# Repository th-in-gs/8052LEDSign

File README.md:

# MSM83C154 ROM Dump

A dump and analysis of the 16 KB internal mask ROM of an OKI MSM83C154
(8051-family) microcontroller, found among the pile of MCS-51 parts in my
[makerspace](https://ashevillemakers.org/)'s electronics supply drawers.

The chips turned out to be preprogrammed. This repository contains the tooling
used to read the ROM out, the dump itself, and an analysis of what the program
does.

A second set of chips from the same drawer, Signetics SCN8031Hs, is covered
in `scn8031/`. They are marked as the ROMless 8031, but their 4 KB internal
ROM holds a stepper motor controller program.

It is a branch of my 8052 LED sign project, which provided the hardware: an
8052 running from SRAM that an ATmega328 loads on its behalf. I'm documenting
that project on my blog,
https://www.blog.montgomerie.net/tags/makerspace-mcu-series/.

## Contents

| Path | What |
|---|---|
| `romdump.bin` | The 16,384-byte ROM dump. Its internal checksum verifies. |
| `ROM_ANALYSIS.md` | What the program does. |
| `romdump_annotated.lst` | Annotated disassembly. |
| `tools/dis51.py` | Minimal recursive-descent 8051 disassembler used for the analysis. |
| `tools/annotate.py` | Generator for the annotated disassemblies. `--annotations MODULE` picks the annotation data. |
| `tools/romdump_annotations.py` | Annotation data for the OKI dump (the default). |
| `scn8031/` | The SCN8031H dump, its analysis and annotated disassembly. |
| `tools/scn8031_annotations.py` | Annotation data for the SCN8031H dump. |
| `mcs51/src/romdump.c` | Dumper, run by the 8052. |
| `avr_host/src/` | AVR host: loads the dumper, runs it, prints the dump over serial. |
| `scripts/capture_romdump.py` | Captures the serial output into a `.bin` file (default `romdump.bin`). |
| `hardware/` | KiCad schematic and PCB of the circuit. |
| `docs/RAM:ROM Shadowing.txt` | Notes on the SRAM address decode the dumper relies on. |

## How the dump works

The MSM83C154 does not latch its EA (External Access) pin at reset, so the
internal ROM can be switched on after the chip has started running external
code:

1. The AVR writes the dumper to SRAM at code address 0x4000, and a stub
   `LJMP 0x4000` at 0x0000.
2. With EA held low, the AVR releases the 8052's reset. The 8052 runs the stub
   from external memory and jumps to the dumper.
3. The AVR raises EA. Code addresses 0x0000–0x3FFF now read the internal ROM.
   Code at 0x4000 and above is still fetched externally.
4. The dumper copies code 0x0000–0x3FFF (MOVC) to data 0x0000–0x3FFF (MOVX).
5. The AVR puts the 8052 back into reset, reads the SRAM, and prints it.

The 8052's EA pin must be wired to AVR pin PD2.

## Running it

This is built with [PlatformIO](https://platformio.org). On Apple Silicon Macs,
PlatformIO's MCS-51 and AVR toolchains need Rosetta.

```
pio run -e mcs51 -t upload
~/.platformio/penv/bin/python scripts/capture_romdump.py [port] [output.bin]
```

Uploading the `mcs51` environment builds the dumper, then builds and uploads
the AVR host with the dumper compiled into it. The capture script resets the
AVR, so the whole sequence (RAM test, load, dump) runs again while it listens.
The serial monitor runs at 38400 baud.

# Copyright

Copyright 2026 James Montgomerie.

See `LICENSE.txt` for license terms.

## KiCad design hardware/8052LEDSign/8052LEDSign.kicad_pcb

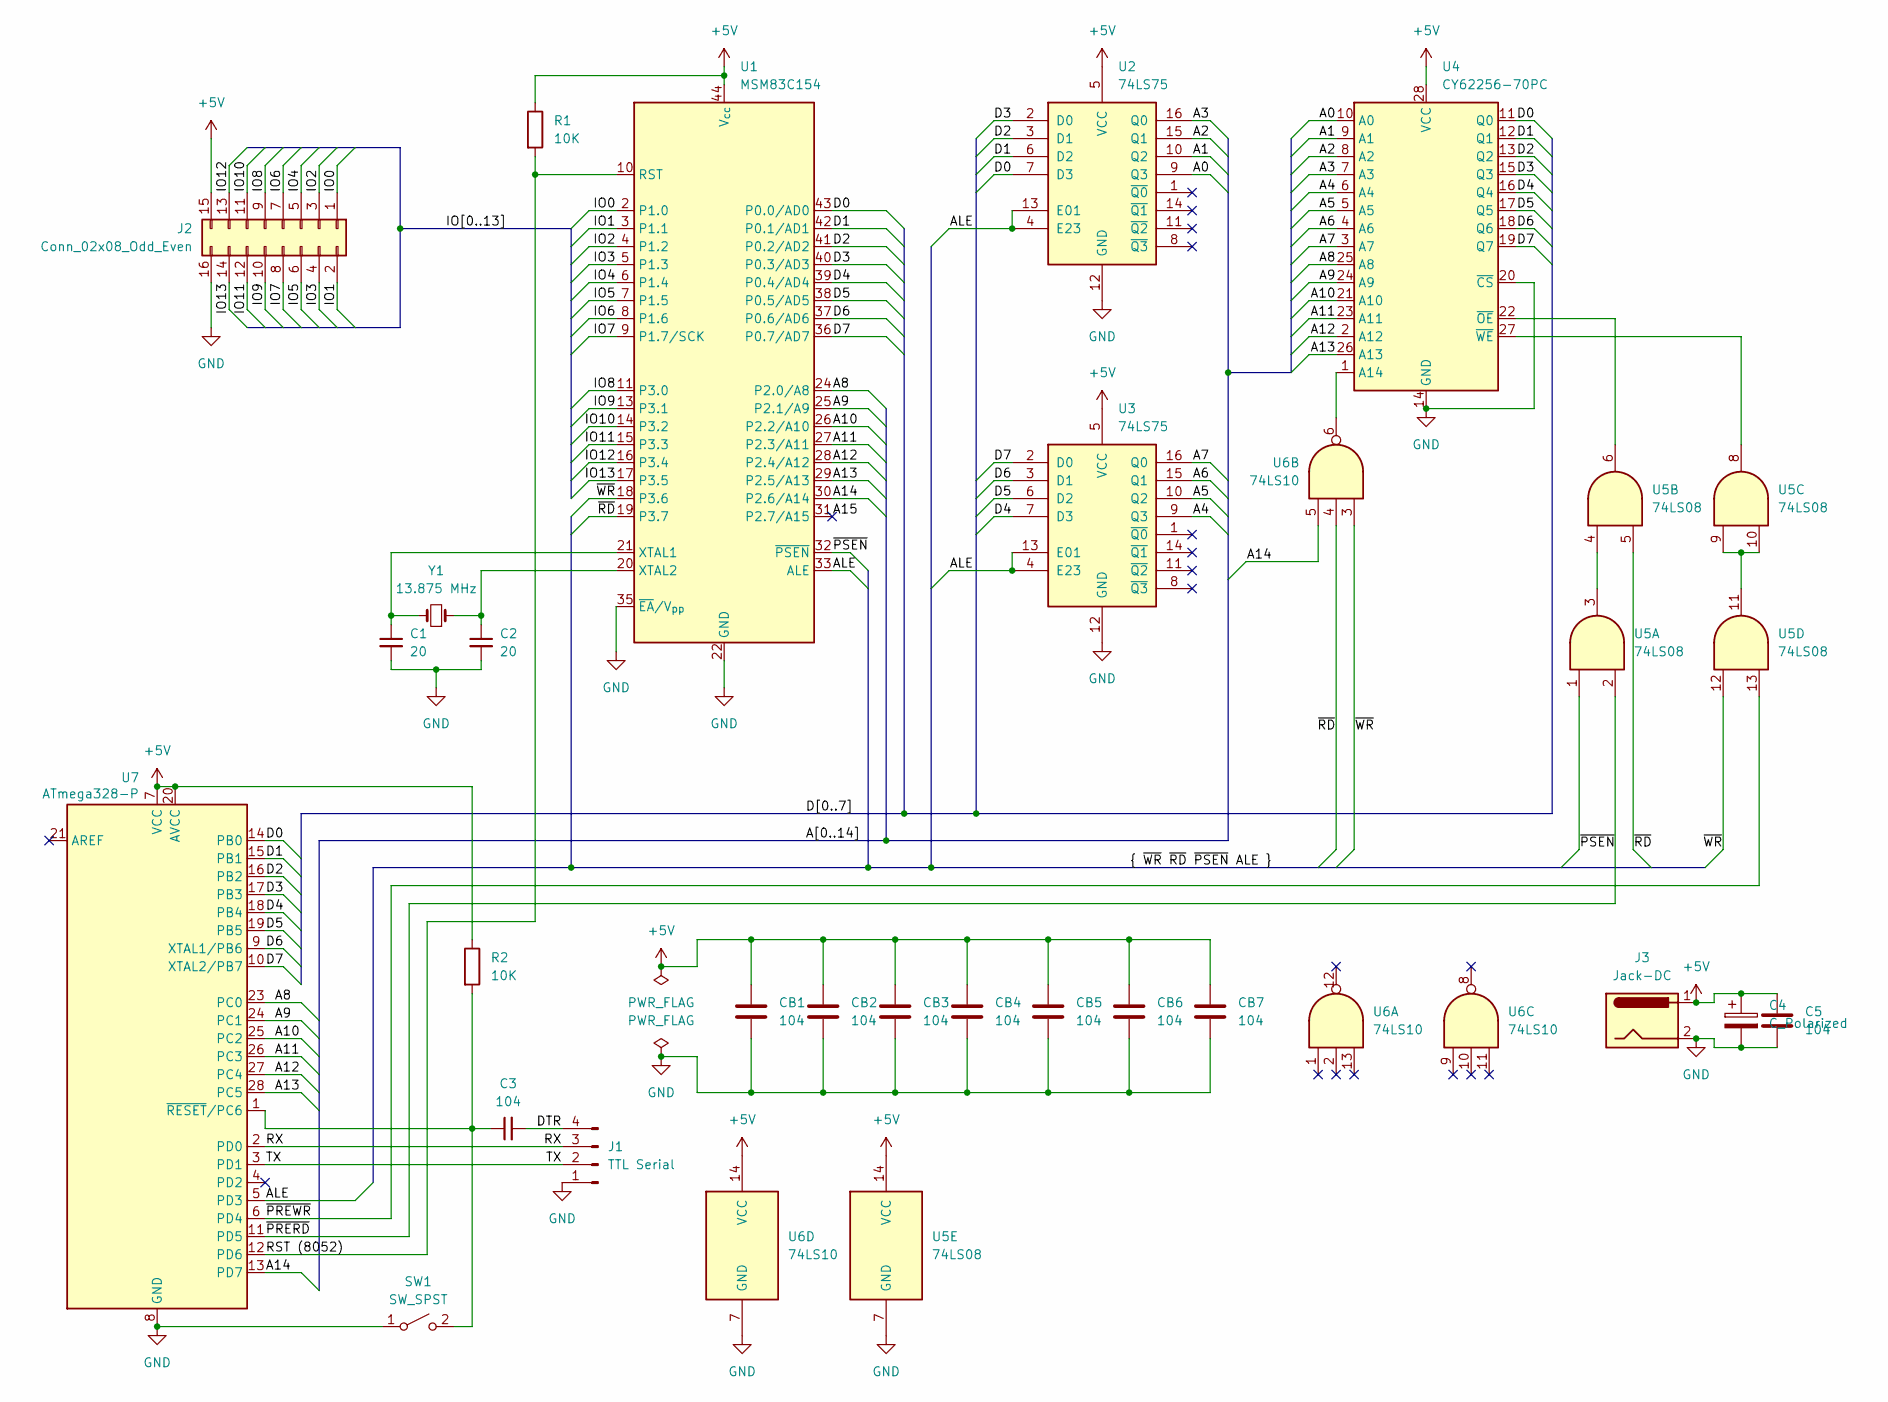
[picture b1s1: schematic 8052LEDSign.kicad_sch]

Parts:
C1, C2: 20; C_Disc_D3.0mm_W1.6mm_P2.50mm
C3, C5: 104; C_Disc_D3.0mm_W1.6mm_P2.50mm
C4: C_Polarized; CP_Radial_D6.3mm_P2.50mm
CB1, CB2, CB3, CB4, CB5, CB6, CB7: 104; C_Disc_D3.0mm_W1.6mm_P2.50mm
J1: TTL Serial; PinSocket_1x04_P2.54mm_Vertical
J2: Conn_02x08_Odd_Even; PinSocket_2x08_P2.54mm_Vertical
J3: Jack-DC; BarrelJack_Horizontal
R1, R2: 10K; R_Axial_DIN0207_L6.3mm_D2.5mm_P10.16mm_Horizontal
SW1: SW_SPST; SW_PUSH_6mm
U1: MSM83C154; PLCC-44_THT-Socket
U2, U3: 74LS75; DIP-16_W7.62mm_Socket
U4: CY62256-70PC; DIP-28_W15.24mm
U5: 74LS08; DIP-14_W7.62mm_Socket
U6: 74LS10; DIP-14_W7.62mm_Socket
U7: ATmega328-P; DIP-28_W7.62mm
Y1: 13.875 MHz; Crystal_HC50_Horizontal

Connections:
+5V: C4.1, C5.1, CB1.1, CB2.1, CB3.1, CB4.1, CB5.1, CB6.1, CB7.1, J2.15, J3.1, R1.1, R2.1, U1.44 (V_{cc}), U2.5 (VCC), U3.5 (VCC), U4.28 (VCC), U5.14 (VCC), U6.14 (VCC), U7.7 (VCC), U7.20 (AVCC)
/A0: U2.9 (Q3), U4.10 (A0)
/A1: U2.10 (Q2), U4.9 (A1)
/A2: U2.15 (Q1), U4.8 (A2)
/A3: U2.16 (Q0), U4.7 (A3)
/A4: U3.9 (Q3), U4.6 (A4)
/A5: U3.10 (Q2), U4.5 (A5)
/A6: U3.15 (Q1), U4.4 (A6)
/A7: U3.16 (Q0), U4.3 (A7)
/A8: U1.24 (P2.0/A8), U4.25 (A8), U7.23 (PC0)
/A9: U1.25 (P2.1/A9), U4.24 (A9), U7.24 (PC1)
/A10: U1.26 (P2.2/A10), U4.21 (A10), U7.25 (PC2)
/A11: U1.27 (P2.3/A11), U4.23 (A11), U7.26 (PC3)
/A12: U1.28 (P2.4/A12), U4.2 (A12), U7.27 (PC4)
/A13: U1.29 (P2.5/A13), U4.26 (A13), U7.28 (PC5)
/A14: U1.30 (P2.6/A14), U6.5, U7.13 (PD7)
/A15: U1.31 (P2.7/A15)
/ALE: U1.33 (ALE), U2.4 (E23), U2.13 (E01), U3.4 (E23), U3.13 (E01), U7.5 (PD3)
/D0: U1.43 (P0.0/AD0), U2.7 (D3), U4.11 (Q0), U7.14 (PB0)
/D1: U1.42 (P0.1/AD1), U2.6 (D2), U4.12 (Q1), U7.15 (PB1)
/D2: U1.41 (P0.2/AD2), U2.3 (D1), U4.13 (Q2), U7.16 (PB2)
/D3: U1.40 (P0.3/AD3), U2.2 (D0), U4.15 (Q3), U7.17 (PB3)
/D4: U1.39 (P0.4/AD4), U3.7 (D3), U4.16 (Q4), U7.18 (PB4)
/D5: U1.38 (P0.5/AD5), U3.6 (D2), U4.17 (Q5), U7.19 (PB5)
/D6: U1.37 (P0.6/AD6), U3.3 (D1), U4.18 (Q6), U7.9 (XTAL1/PB6)
/D7: U1.36 (P0.7/AD7), U3.2 (D0), U4.19 (Q7), U7.10 (XTAL2/PB7)
/DTR: C3.2, J1.4
/IO0: J2.1, U1.2 (P1.0)
/IO1: J2.2, U1.3 (P1.1)
/IO2: J2.3, U1.4 (P1.2)
/IO3: J2.4, U1.5 (P1.3)
/IO4: J2.5, U1.6 (P1.4)
/IO5: J2.6, U1.7 (P1.5)
/IO6: J2.7, U1.8 (P1.6)
/IO7: J2.8, U1.9 (P1.7/SCK)
/IO8: J2.9, U1.11 (P3.0)
/IO9: J2.10, U1.13 (P3.1)
/IO10: J2.11, U1.14 (P3.2)
/IO11: J2.12, U1.15 (P3.3)
/IO12: J2.13, U1.16 (P3.4)
/IO13: J2.14, U1.17 (P3.5)
/RST (8052): R1.2, U1.10 (RST), U7.12 (PD6)
/RX: J1.3, U7.2 (PD0)
/TX: J1.2, U7.3 (PD1)
/~PRERD: U5.2, U7.11 (PD5)
/~PREWR: U5.13, U7.6 (PD4)
/~PSEN: U1.32 (~PSEN), U5.1
/~RD: U1.19 (P3.7), U5.5, U6.4
/~WR: U1.18 (P3.6), U5.12, U6.3
GND: C1.2, C2.2, C4.2, C5.2, CB1.2, CB2.2, CB3.2, CB4.2, CB5.2, CB6.2, CB7.2, J1.1, J2.16, J3.2, SW1.1 (A), U1.22 (GND), U1.35 (~EA/V_{pp}), U2.12 (GND), U3.12 (GND), U4.14 (GND), U4.20 (~CS), U5.7 (GND), U6.7 (GND), U7.8 (GND), U7.22 (GND)
unnamed: C3.1, R2.2, SW1.2 (B), U7.1 (~RESET/PC6)
unnamed: C1.1, U1.21 (XTAL1), Y1.2
unnamed: C2.1, U1.20 (XTAL2), Y1.1
unnamed: U4.1 (A14), U6.6
unnamed: U4.22 (~OE), U5.6
unnamed: U4.27 (~WE), U5.8
unnamed: U5.3, U5.4
unnamed: U5.9, U5.10, U5.11

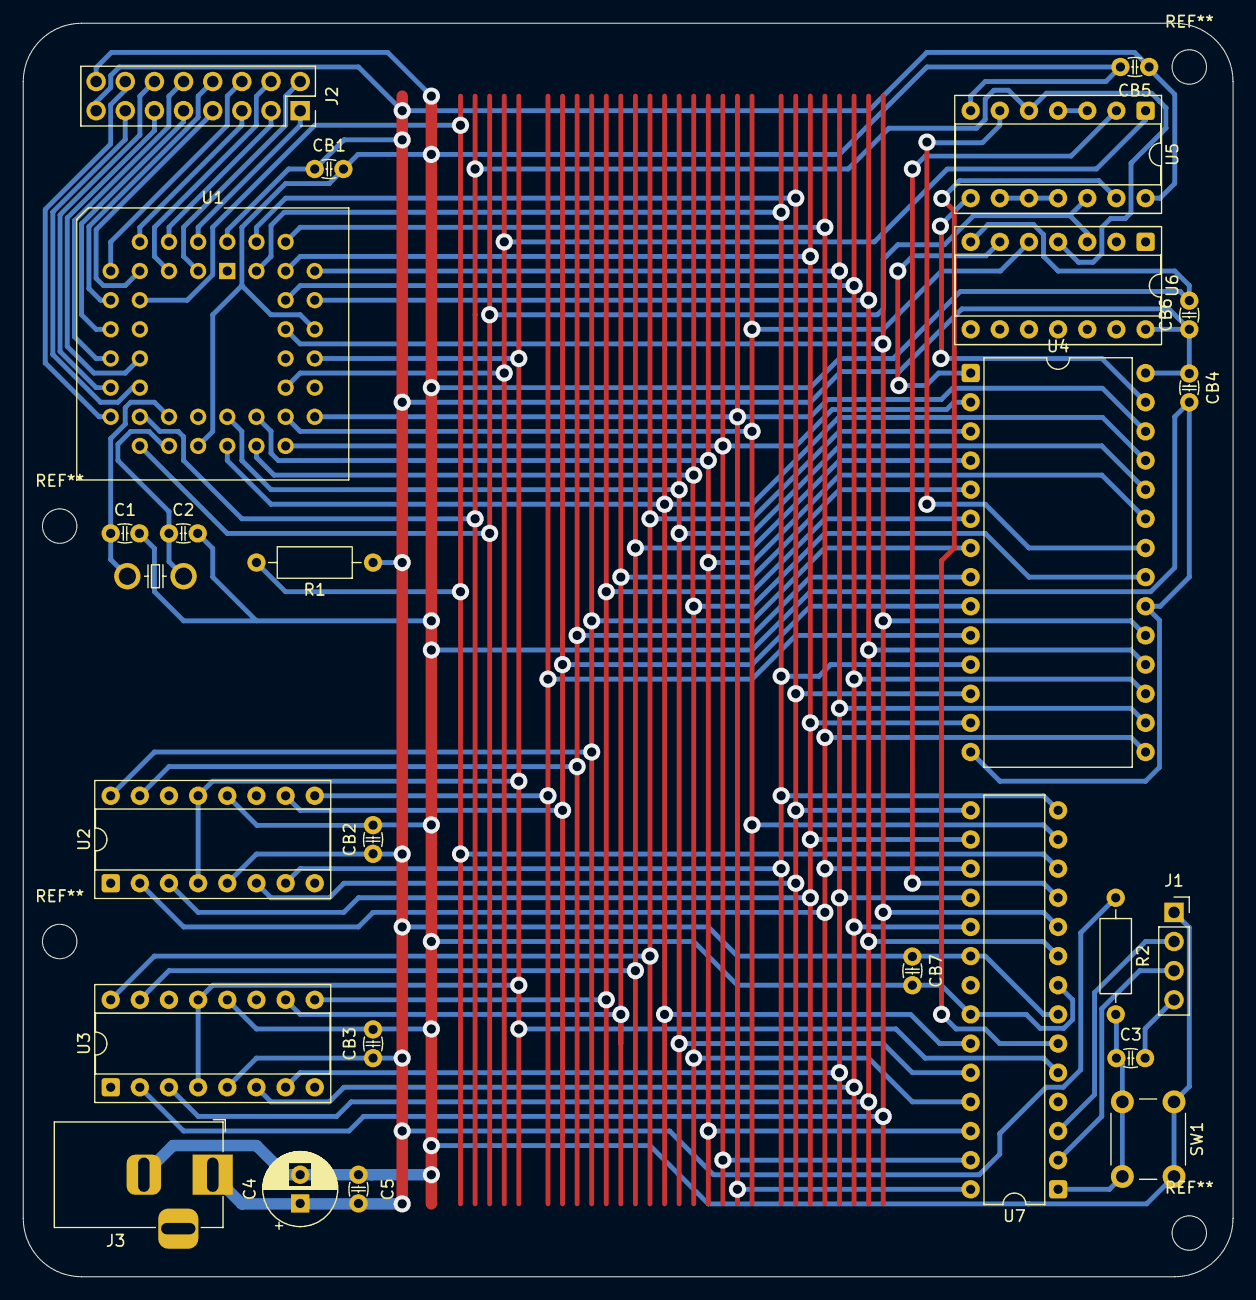
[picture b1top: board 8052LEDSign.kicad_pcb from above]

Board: 2 copper layers, 105.4 x 109.2 mm, 26 parts (1 on the bottom side), 57 nets.

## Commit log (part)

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2026-06-23 PCB layout and mill test PCB. PCB is not currently iptimized for milling.
